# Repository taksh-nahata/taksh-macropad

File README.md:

# Nexus-4 (my first piece of hardware)

Okay, okay, okay. Let me introduce you to Nexus-4, a custom 4-key macropad. It features an inverted-T arrow key layout, a 128x32 OLED display, and a 3D-printed sandwich-mount case. So I run the the software of this on a Seeed Studio XIAO RP2040 that runs my custom QMK firmware. I've even made some simple ASCII art animations(currently very simple tho)!

---

## Completed Build & Demo

### Video Demonstration
[Watch the Nexus-4 in action](https://drive.google.com/file/d/1Elsz5yWcckBbZZuh22iVLzsOhnGGIkVX/view?usp=sharing)

---

## Some Features
* **Custom 3D-Printed Enclosure:** So basically, I made a two-piece sandwich-mount case (Top Plate + Bottom Case) which are connected together using screws at the corner.
* **Interactive OLED Animation:** I've got a 0.91" 128x32 I2C OLED display at the top middle of the macropad, which shows ASCII animations that I made, and they react to your keystrokes.

---

## Hardware & CAD Design

The cadded box I made for the macropad is a sandwich-mount structure, and I made it on Fusion 360. The PCB rests inside this enclosure, and it is topped by the Top Plate, which is secured using screws at the four corners. I've also made a side cutout in the Bottom Case, to give access to the RP2040's USB-C connector.

---

## PCB & Schematic

I made the PCB in KiCad completely. I used direct-pin connections to simplify the overall layout and also reduce the number of components I need.

* **Microcontroller:** Seeed Studio XIAO RP2040
* **Display Interface:** I2C (SDA on `GP6`, SCL on `GP7`)
* **Switch Routing:**
  * **Up Switch (SW1):** `GP2` (Pin D8)
  * **Left Switch (SW2):** `GP3` (Pin D10)
  * **Down Switch (SW3):** `GP4` (Pin D9)
  * **Right Switch (SW4):** `GP1` (Pin D7)

---

## Firmware & OLED Logic

The firmware is compiled with QMK for the RP2040 (`promicro_rp2040` target).

Layout:
* `KC_UP` (Up Arrow)
* `KC_LEFT` (Left Arrow)
* `KC_DOWN` (Down Arrow)
* `KC_RIGHT` (Right Arrow)

* **Keymaps:** This is pretty standard and straight forward. It's just mapped to standard navigation keys (`KC_UP`, `KC_LEFT`, `KC_DOWN`, `KC_RIGHT`).
* **OLED Engine:** The OLED screen shows an inverted (because the OLED is positioned the wrong way on the PCB), and centered ASCII text and animation. When there are no keys being pressed, there is a simple breathing sleep animation (`zZz`) and this cycles continuously. Pressing any key triggers `process_record_user()` to update the active expression in the direction of input (`owo`, `>_<`, `o_o`, `-w-`).

---

## Bill of Materials (BOM)

This does not include all tools I used to build this. Only the components which are directly on the macropad. To view a full list of materials, you can view the BOM file I've attached to this repo.

| Category | Component | Quantity |
| :--- | :--- | :--- |
| **Electronics** | Seeed Studio XIAO RP2040 | 1 |
| **Electronics** | 0.91" 128x32 I2C OLED Display | 1 |
| **Electronics** | Cherry MX-Compatible Switches | 4 |
| **Electronics** | Custom 2-Layer PCB | 1 |
| **Hardware** | 3D-Printed Top Plate | 1 |
| **Hardware** | 3D-Printed Bottom Case | 1 |
| **Hardware** | M4 (or M3) Screws & Nuts | 4 |
| **Keycaps** | 1u Keycaps | 4 |

---

## How can you make this?

1. **Surface-Mount the microchip:** Start by soldering the RP2040 chip directly, flat to the PCB pads, using its castellated edges. This is to ensure that the chip is not raised any more than necessary to give enough spaces for the pins of the switches.
2. **Mount the OLED:** Remove the plastic collar from the 4 pin header and then solder the bare pins between the PCB and the OLED. You will need to solder both sides, on the back side of the PCB and on top of the OLED, to ensure the connection is secure.
3. **Mount the Switches:** Fit the switches perfectly into the holes from the top of the Top Plate (you will hear a click), and then you can align the PCB with the pins of the switches. Once perfectly aligned and all pins are somewhat through the holes of the PCB, you can solder them all to the PCB. Feed 2-3 mm of solder for this.
4. **Enclosure Assembly:** You're basically done! Just drop the PCB assembly into the bottom case and then secure the sandwich using four corner bolts and nuts.
5. **Flash Firmware:**
   * Enter bootloader mode by holding the **Boot** key or grounding `GP26` (`D0`) on startup to mount the `RPI-RP2` drive.
   * Compile and copy the `.uf2` file:
     ```bash
     qmk compile -kb taksh_macropad -km default
     ```
   * Drag and drop `Nexus-4_default` into `RPI-RP2`.

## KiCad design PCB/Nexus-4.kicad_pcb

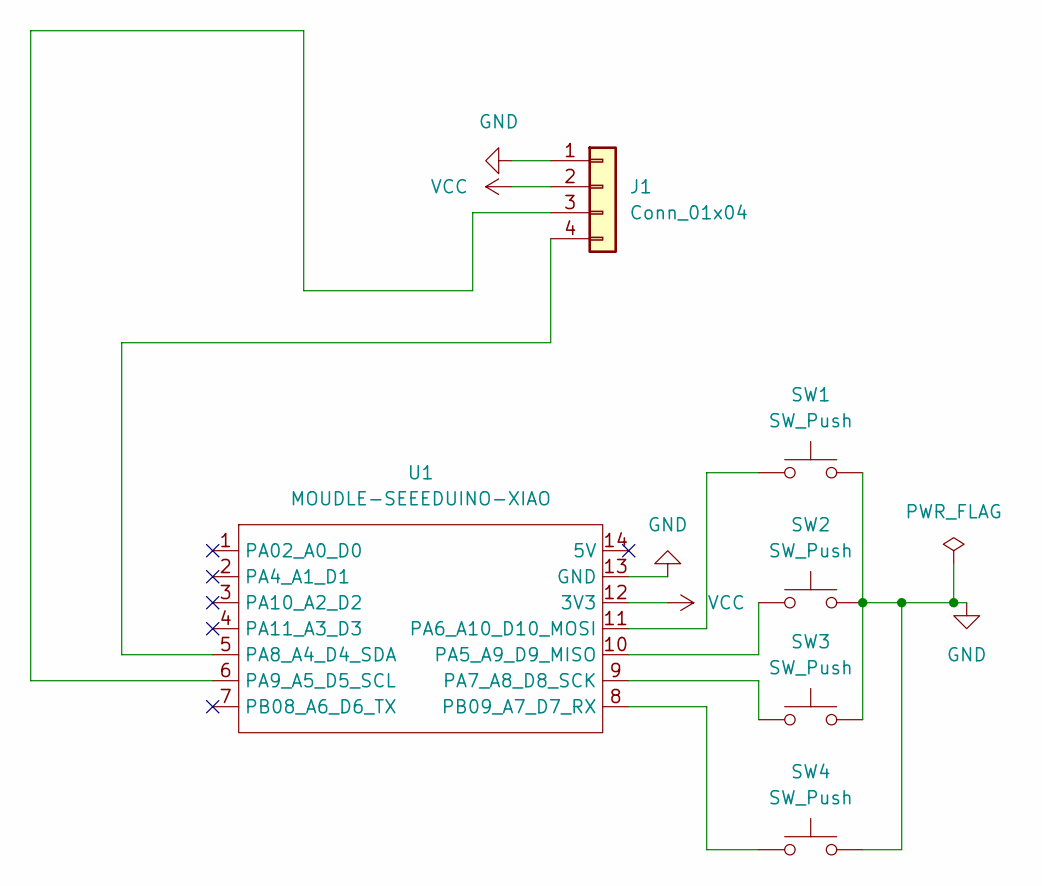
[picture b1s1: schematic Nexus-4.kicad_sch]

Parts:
J1: Conn_01x04; SSD1306-0.91-OLED-4pin-128x32
SW1, SW2, SW3, SW4: SW_Push; SW_Cherry_MX_1.00u_PCB
U1: MOUDLE-SEEEDUINO-XIAO; XIAO-Generic-Hybrid-14P-2.54-21X17.8MM

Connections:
GND: J1.1, SW1.2, SW2.2, SW3.2, SW4.2, U1.13 (GND)
unnamed: J1.3, U1.6 (PA9_A5_D5_SCL)
unnamed: J1.4, U1.5 (PA8_A4_D4_SDA)
unnamed: SW2.1, U1.10 (PA5_A9_D9_MISO)
unnamed: SW1.1, U1.11 (PA6_A10_D10_MOSI)
unnamed: SW3.1, U1.9 (PA7_A8_D8_SCK)
unnamed: SW4.1, U1.8 (PB09_A7_D7_RX)
VCC: J1.2, U1.12 (3V3)

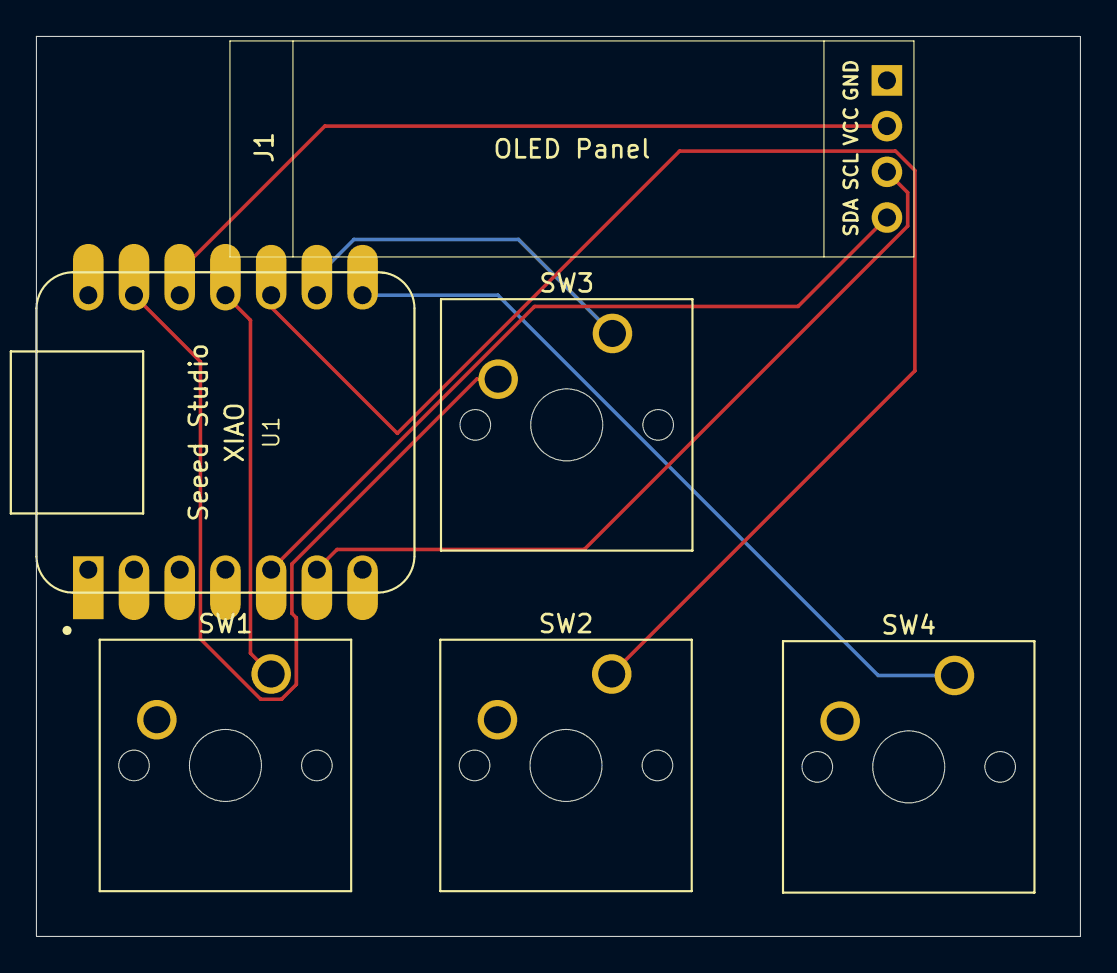
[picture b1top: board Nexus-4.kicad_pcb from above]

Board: 2 copper layers, 58.0 x 50.0 mm, 6 parts (0 on the bottom side), 8 nets.

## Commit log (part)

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2026-05-29 Add 3-key QMK firmware source code
2026-06-01 Updated Entire Macropad to include all production details and original parts
2026-06-01 fixed readme
2026-06-01 fixed naming issue
2026-06-01 add kicad prl
2026-06-02 Fix formatting
2026-06-09 fixed changes asked
2026-06-09 adjusted some placements
2026-06-11 fixed some changes and made it look more asthetic overall
2026-06-15 added BOM and updated README
